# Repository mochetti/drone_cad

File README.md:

# drone_cad
 Arquivos CAD para o projeto do drone diy

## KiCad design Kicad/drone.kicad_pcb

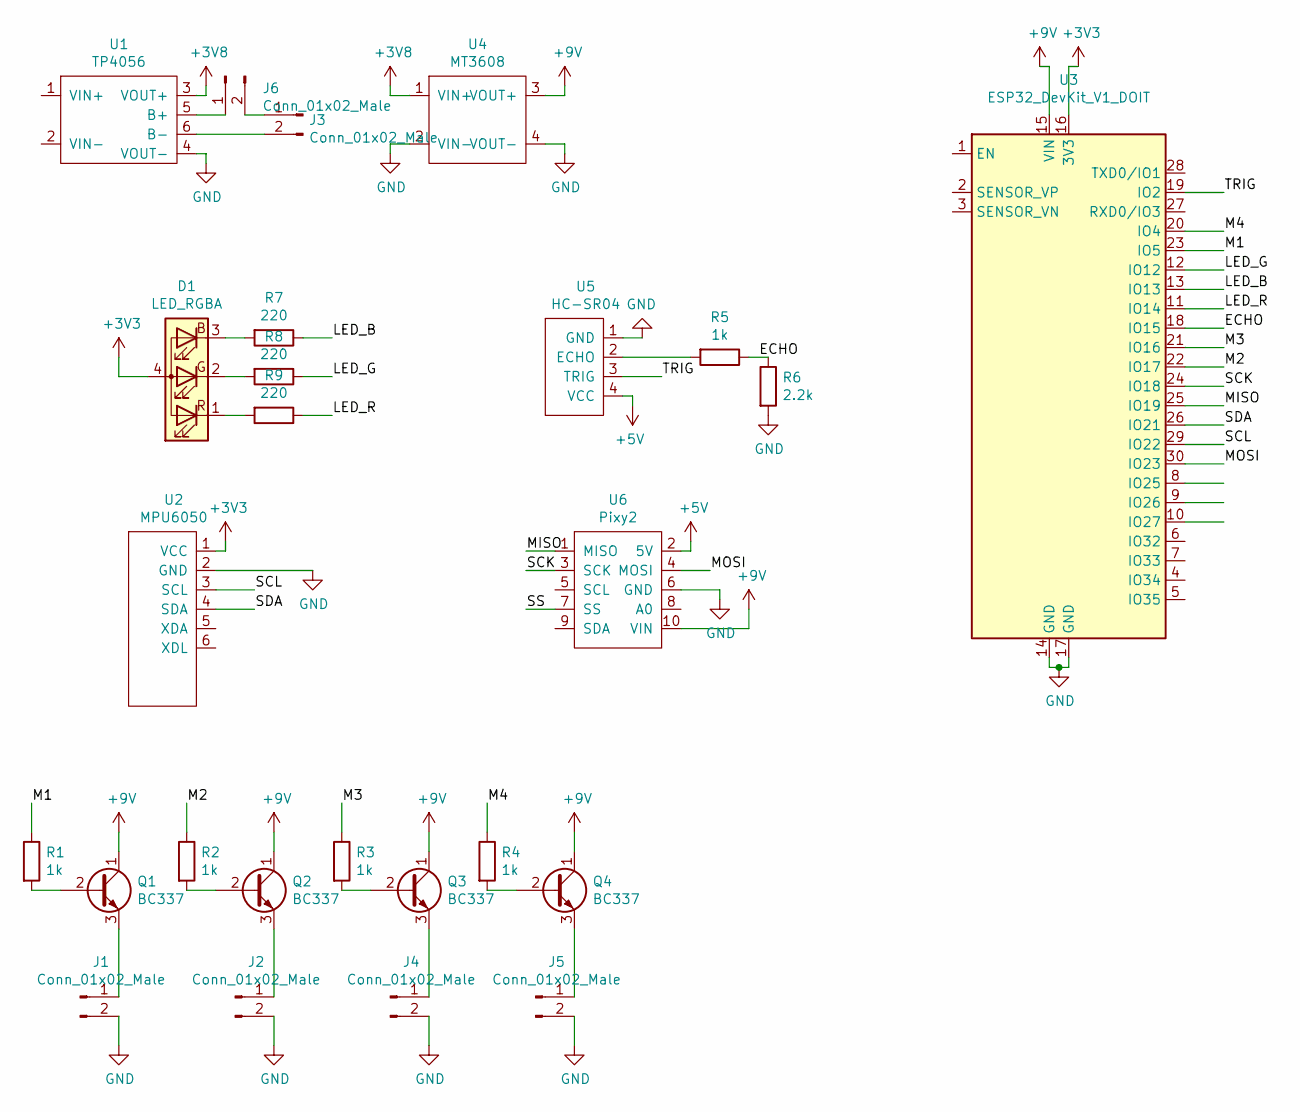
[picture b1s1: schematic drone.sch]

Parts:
D1: LED_RGBA; PinHeader_1x04_P2.54mm_Vertical
J1, J2, J3, J4, J5: Conn_01x02_Male; JST_PH_B2B-PH-K_1x02_P2.00mm_Vertical
J6: Conn_01x02_Male; PinHeader_1x02_P2.54mm_Vertical
Q1, Q2, Q3, Q4: BC337; PinHeader_1x03_P2.54mm_Vertical
R1, R2, R3, R4, R5: 1k; R_Axial_DIN0204_L3.6mm_D1.6mm_P5.08mm_Horizontal
R6: 2.2k; R_Axial_DIN0204_L3.6mm_D1.6mm_P5.08mm_Horizontal
R7, R8, R9: 220; R_Axial_DIN0204_L3.6mm_D1.6mm_P5.08mm_Horizontal
U1: TP4056
U2: MPU6050
U3: ESP32_DevKit_V1_DOIT; ESP32_Module
U4: MT3608
U5: HC-SR04
U6: Pixy2

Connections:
+3V3: D1.4 (A), U2.1 (VCC), U3.16 (3V3)
+3V8: U1.3 (VOUT+), U4.1 (VIN+)
+5V: U5.4 (VCC), U6.2 (5V)
+9V: Q1.1 (C), Q2.1 (C), Q3.1 (C), Q4.1 (C), U3.15 (VIN), U4.3 (VOUT+), U6.10 (VIN)
/ECHO: R5.1, R6.1, U3.18 (IO15)
/LED_B: R7.1, U3.13 (IO13)
/LED_G: R8.1, U3.12 (IO12)
/LED_R: R9.1, U3.11 (IO14)
/M1: R1.1, U3.23 (IO5)
/M2: R2.1, U3.22 (IO17)
/M3: R3.1, U3.21 (IO16)
/M4: R4.1, U3.20 (IO4)
/MISO: U3.25 (IO19), U6.1 (MISO)
/MOSI: U3.30 (IO23), U6.4 (MOSI)
/SCK: U3.24 (IO18), U6.3 (SCK)
/SCL: U2.3 (SCL), U3.29 (IO22)
/SDA: U2.4 (SDA), U3.26 (IO21)
/SS: U6.7 (SS)
/TRIG: U3.19 (IO2), U5.3 (TRIG)
GND: J1.2, J2.2, J4.2, J5.2, R6.2, U1.4 (VOUT-), U2.2 (GND), U3.14 (GND), U3.17 (GND), U4.2 (VIN-), U4.4 (VOUT-), U5.1 (GND), U6.6 (GND)
unnamed: D1.1 (RK), R9.2
unnamed: D1.2 (GK), R8.2
unnamed: D1.3 (BK), R7.2
unnamed: J1.1, Q1.3 (E)
unnamed: J2.1, Q2.3 (E)
unnamed: J3.1, J6.2
unnamed: J3.2, U1.6 (B-)
unnamed: J4.1, Q3.3 (E)
unnamed: J5.1, Q4.3 (E)
unnamed: J6.1, U1.5 (B+)
unnamed: Q1.2 (B), R1.2
unnamed: Q2.2 (B), R2.2
unnamed: Q3.2 (B), R3.2
unnamed: Q4.2 (B), R4.2
unnamed: R5.2, U5.2 (ECHO)

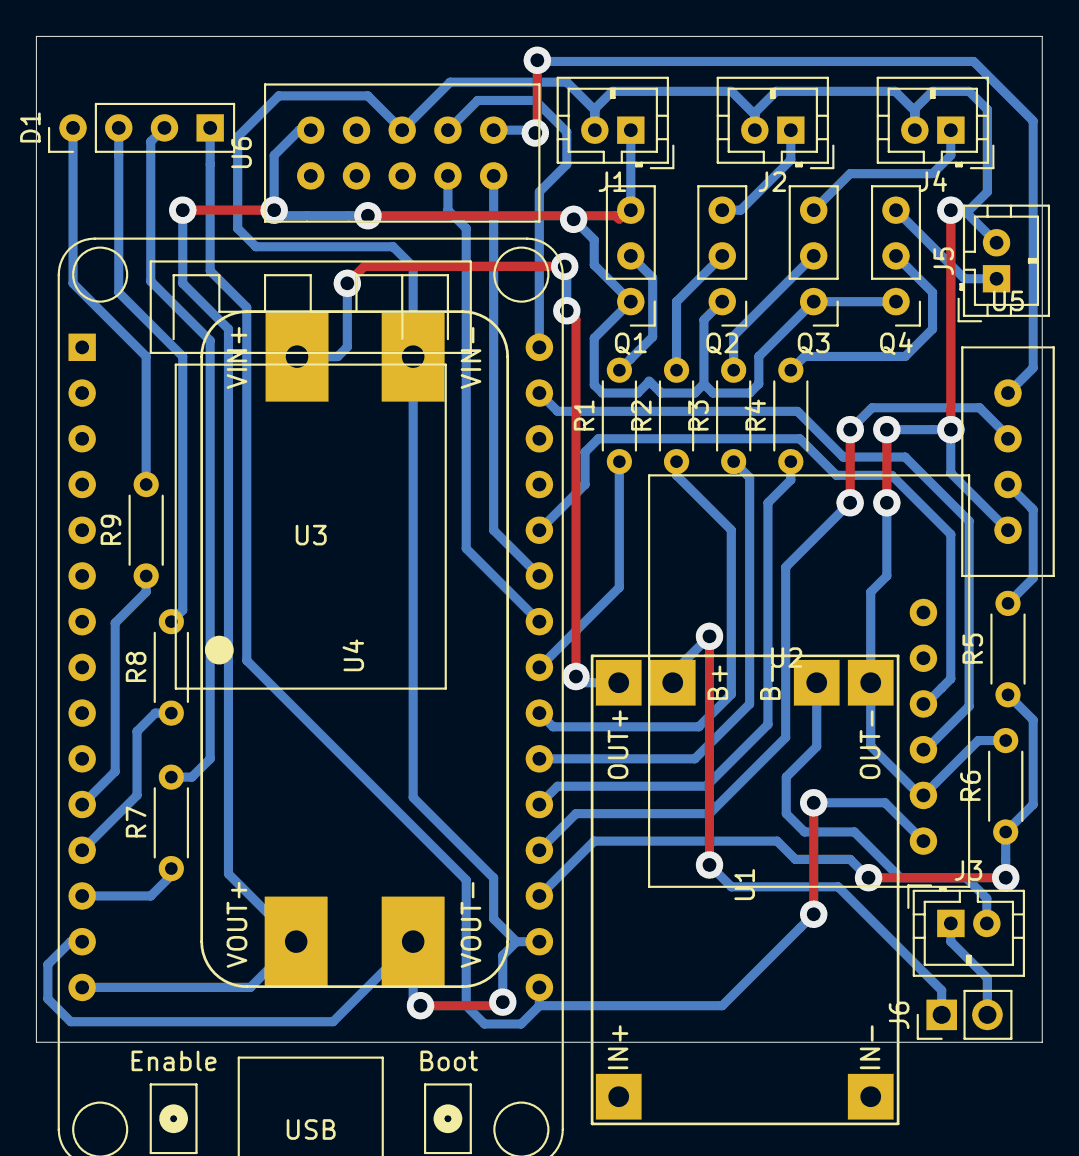
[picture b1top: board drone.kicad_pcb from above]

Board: 2 copper layers, 55.9 x 55.9 mm, 26 parts (0 on the bottom side), 34 nets.

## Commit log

2021-04-26 folder update
2022-01-01 add kicad files
